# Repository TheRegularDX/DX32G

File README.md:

# DX32G
ESP32S3 based board with built in USB to serial adapter, micro SD card reader, and I2C OLED connection.

## Features
- WiFi and BLE
- x25 GPIO pins
- x1 WS2812B addresable RGB led
- x1 Micro SD card reader
- x1 0,96 OLED connection
- CH340N USB to serial adapter

## Programming
Supports Arduino IDE, PlattformIO and CircuitPython.

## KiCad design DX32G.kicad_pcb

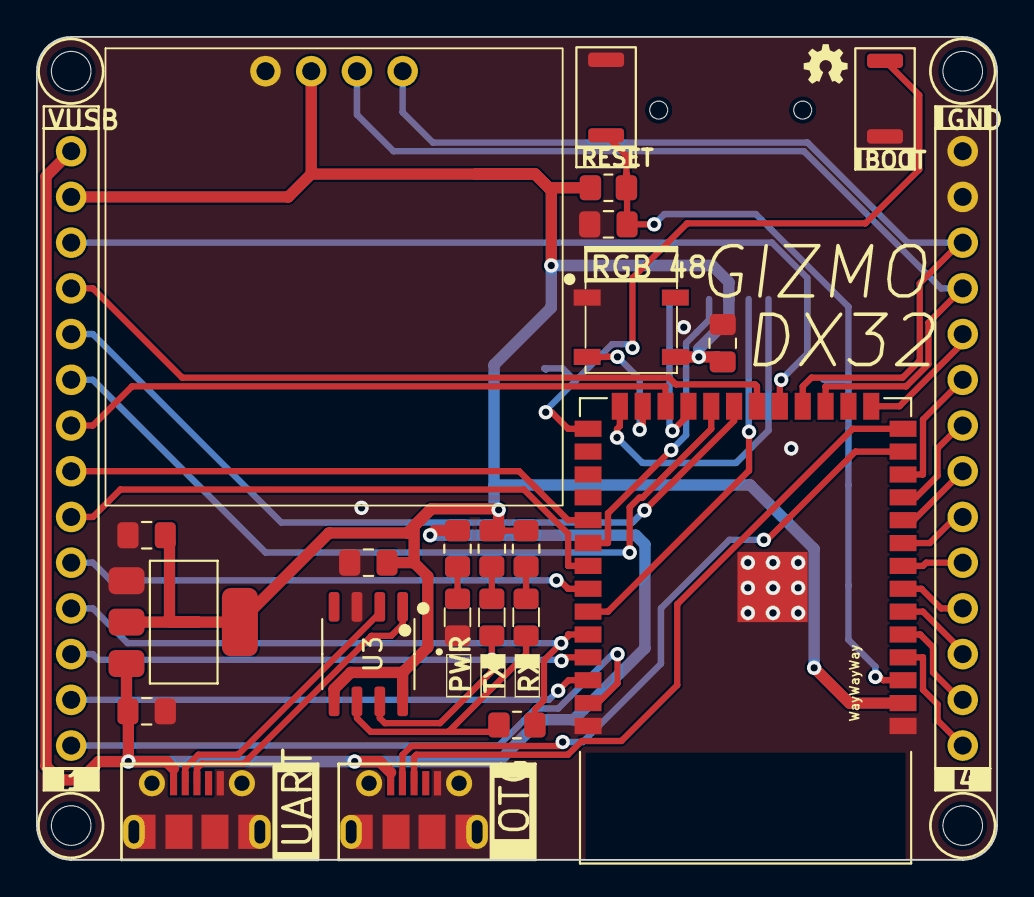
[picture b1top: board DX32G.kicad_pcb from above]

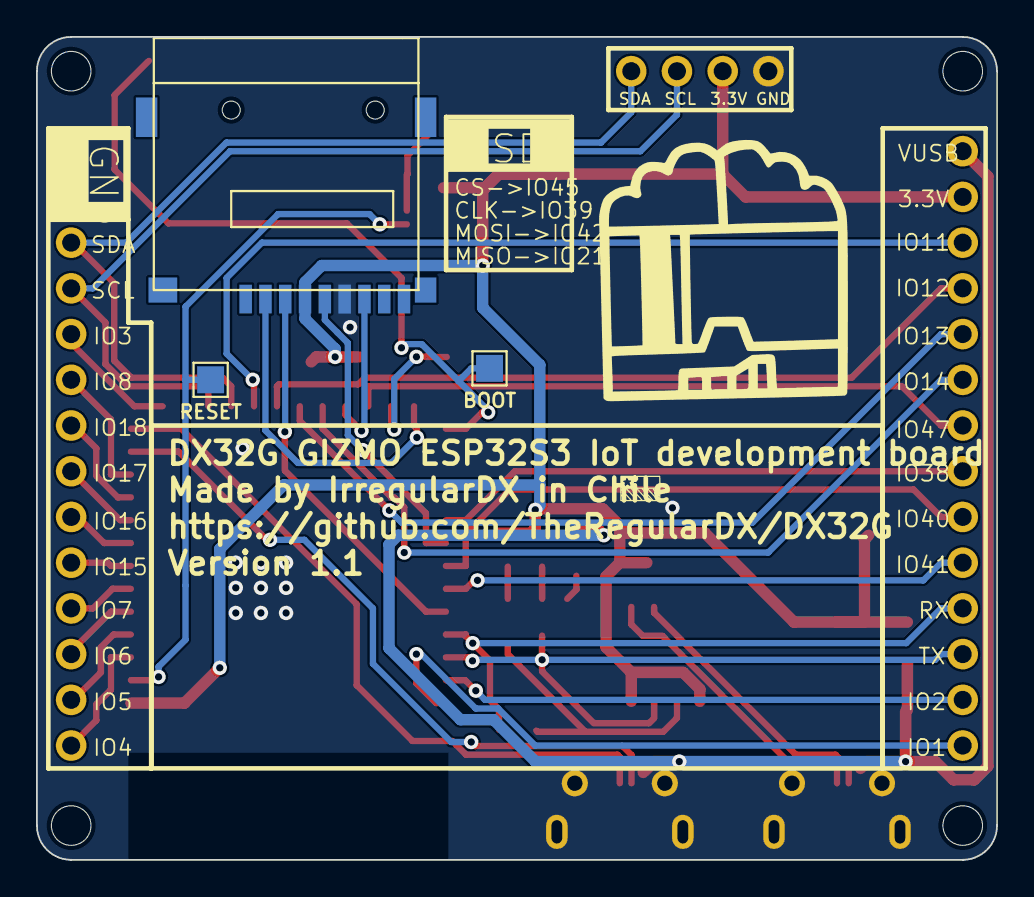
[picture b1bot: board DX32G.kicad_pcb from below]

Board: 2 copper layers, 53.3 x 45.7 mm, 34 parts (5 on the bottom side), 42 nets.

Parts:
BOOT: BOOT; TestPoint_Pad_1.5x1.5mm
C1: 1uF; C_0805_2012Metric_Pad1.18x1.45mm_HandSolder
C2, C3, C4, C5: 10uF; C_0805_2012Metric_Pad1.18x1.45mm_HandSolder
D1, D2, D3: LED; LED_0805_2012Metric_Pad1.15x1.40mm_HandSolder
D4: WS2812B; LED_WS2812B_PLCC4_5.0x5.0mm_P3.2mm
Flag: LOGO
HOLE: MountingHole_2.2mm_M2_DIN965
J1, J7: USB_B_Micro; USB_Micro-B_Molex-105017-0001
J2: MicroSD Card; 112J-TDAR-R01
J3: RIGHT; PinHeader_1x14_P2.54mm_Vertical
J4: LEFT; PinHeader_1x14_P2.54mm_Vertical
OSH: LOGO
R1: 10k; R_0805_2012Metric_Pad1.20x1.40mm_HandSolder
R2, R3, R4, R5: 1k; R_0805_2012Metric_Pad1.20x1.40mm_HandSolder
RESET: RESET; TestPoint_Pad_1.5x1.5mm
SW1: reset; SW_Push_SPST_NO_Alps_SKRK
SW2: boot; SW_Push_SPST_NO_Alps_SKRK
U1: ESP32-S3-WROOM-1
U2: AMS1117-3.3; SOT-223-3_TabPin2
U3: CH340N; SOP-8_3.9x4.9mm_P1.27mm
U4: SSD1306_OLED
hole2, hole3, hole4: MountingHole_2.2mm_M2_DIN965
logo: LOGO

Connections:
+3.3V: C3.1, C4.2, C5.2, D4.1 (VDD), J2.4 (4-VDD), J4.2, R1.1, R2.2, R3.2, U1.2 (3V3), U2.2 (VO), U3.5 (VCC), U3.8 (V3), U4.2 (VCC)
+5V: C2.1, J1.1 (VBUS), J4.1, J7.1 (VBUS), R5.2, U2.3 (VI)
/BOOT: BOOT.1, SW2.1, U1.27 (IO0)
/GPIO1: J4.14, U1.39 (IO1)
/GPIO2: J4.13, U1.38 (IO2)
/GPIO3: J3.10, U1.15 (IO3)
/GPIO4: J3.1, U1.4 (IO4)
/GPIO5: J3.2, U1.5 (IO5)
/GPIO6: J3.3, U1.6 (IO6)
/GPIO7: J3.4, U1.7 (IO7)
/GPIO8: J3.9, U1.12 (IO8)
/GPIO9_SCL: J3.11, U1.17 (IO9), U4.3 (SCL)
/GPIO10_SDA: J3.12, U1.18 (IO10), U4.4 (SDA)
/GPIO11: J4.3, U1.19 (IO11)
/GPIO12: J4.4, U1.20 (IO12)
/GPIO13: J4.5, U1.21 (IO13)
/GPIO14: J4.6, U1.22 (IO14)
/GPIO15: J3.5, U1.8 (IO15)
/GPIO16: J3.6, U1.9 (IO16)
/GPIO17: J3.7, U1.10 (IO17)
/GPIO18: J3.8, U1.11 (IO18)
/GPIO38: J4.8, U1.31 (IO38)
/GPIO40: J4.9, U1.33 (IO40)
/GPIO41: J4.10, U1.34 (IO41)
/GPIO47: J4.7, U1.24 (IO47)
/IO_RX: J4.11, R4.1, U1.36 (RXD0)
/IO_TX: D3.1 (K), J4.12, U1.37 (TXD0), U3.7 (RXD)
/RESET: C1.1, R1.2, RESET.1, SW1.1, U1.3 (EN)
/RGB_LED: D4.4 (DIN), U1.25 (IO48)
/SD_CLK: J2.5 (5-CLK), U1.32 (IO39)
/SD_CS: J2.2 (2-CD/DAT3), U1.26 (IO45)
/SD_MISO_DO: J2.7 (7-DAT0), U1.23 (IO21)
/SD_MOSI_DI: J2.3 (3-CMD), U1.35 (IO42)
/USB_D+: J1.3 (D+), U1.14 (IO20)
/USB_D-: J1.2 (D-), U1.13 (IO19)
GND: C1.2, C2.2, C3.2, C4.1, C5.1, D1.1 (K), D4.3 (VSS), J1.5 (GND), J1.6 (Shield), J2.6 (6-VSS), J3.13, J3.14, J7.5 (GND), J7.6 (Shield), SW1.2, SW2.2, U1.1 (GND), U1.40 (GND), U1.41 (GND), U2.1 (GND), U3.3 (GND), U4.1 (GND)
unnamed: D1.2 (A), R5.1
unnamed: D2.2 (A), R2.1
unnamed: D2.1 (K), R4.2, U3.6 (TXD)
unnamed: D3.2 (A), R3.1
unnamed: J7.3 (D+), U3.1 (UD+)
unnamed: J7.2 (D-), U3.2 (UD-)

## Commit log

2024-08-31 Rename aughaugh.png to flag.png
2026-02-09 fixed minor silkscreen mistakes
